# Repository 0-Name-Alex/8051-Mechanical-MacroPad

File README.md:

# ⌨️ 8051 Mechanical Macro Pad

<div align="center">

**A custom mechanical macro keypad engineered around the classic 8051 microcontroller architecture.**  
Designed in KiCad EDA — featuring mechanical switch matrix, diode isolation, and programmable macro functionality.

[-orange)](#)

</div>

---

## 🎯 Project Overview

This project is a dedicated **hardware macro pad** powered by an 8051 microcontroller. Designed for productivity, gaming macros, and shortcut triggering, it provides tactile mechanical switch input with hardware-level debouncing and matrix scanning.

### ✨ Hardware Highlights

- 🔘 **Mechanical Switches**: Footprints compatible with standard Cherry MX / Kailh / Gateron style switches.
- ⚡ **Anti-Ghosting Matrix**: Individual diode isolation for each switch, supporting N-key rollover across macro triggers.
- 🧠 **8051 Core**: Demonstrates hardware implementation and register-level firmware scanning on the classic embedded 8051 architecture.
- 📐 **Compact Form Factor**: Designed for minimal desktop footprint alongside a primary keyboard.

---

## 📊 Development Status

```
[████████████████████] 100%  Schematic Design & Netlist (Done)
[██████████████░░░░░░]  70%  PCB Layout & Trace Routing (In Progress 🔄)
[░░░░░░░░░░░░░░░░░░░░]   0%  Final Fabrication Gerbers & BOM (Upcoming)
[░░░░░░░░░░░░░░░░░░░░]   0%  Firmware Implementation & Keymapping (Upcoming)
```

> ⚠️ **Note:** This project is actively being routed and finalized in KiCad. Final revision Gerbers and assembly photos will be added upon manufacturing!

---

## 📁 Repository Files

| File | Description |
|---|---|
| `MEchanical Macro pad.kicad_pro` | Master KiCad project file |
| `MEchanical Macro pad.kicad_sch` | Full electrical schematic diagram & switch matrix netlist |
| `MEchanical Macro pad.kicad_pcb` | Board layout, copper traces, footprints, and silk screen |

---

## 🛠️ Opening the Project

1. Install [**KiCad EDA**](https://www.kicad.org/) (version 7.0 or later recommended).
2. Clone this repository:
   ```bash
   git clone https://github.com/0-Name-Alex/8051-Mechanical-MacroPad.git
   ```
3. Open `MEchanical Macro pad.kicad_pro` in KiCad to view both the schematic and PCB layout editor.

---

## 📄 License

Open-source hardware project licensed under the MIT License.

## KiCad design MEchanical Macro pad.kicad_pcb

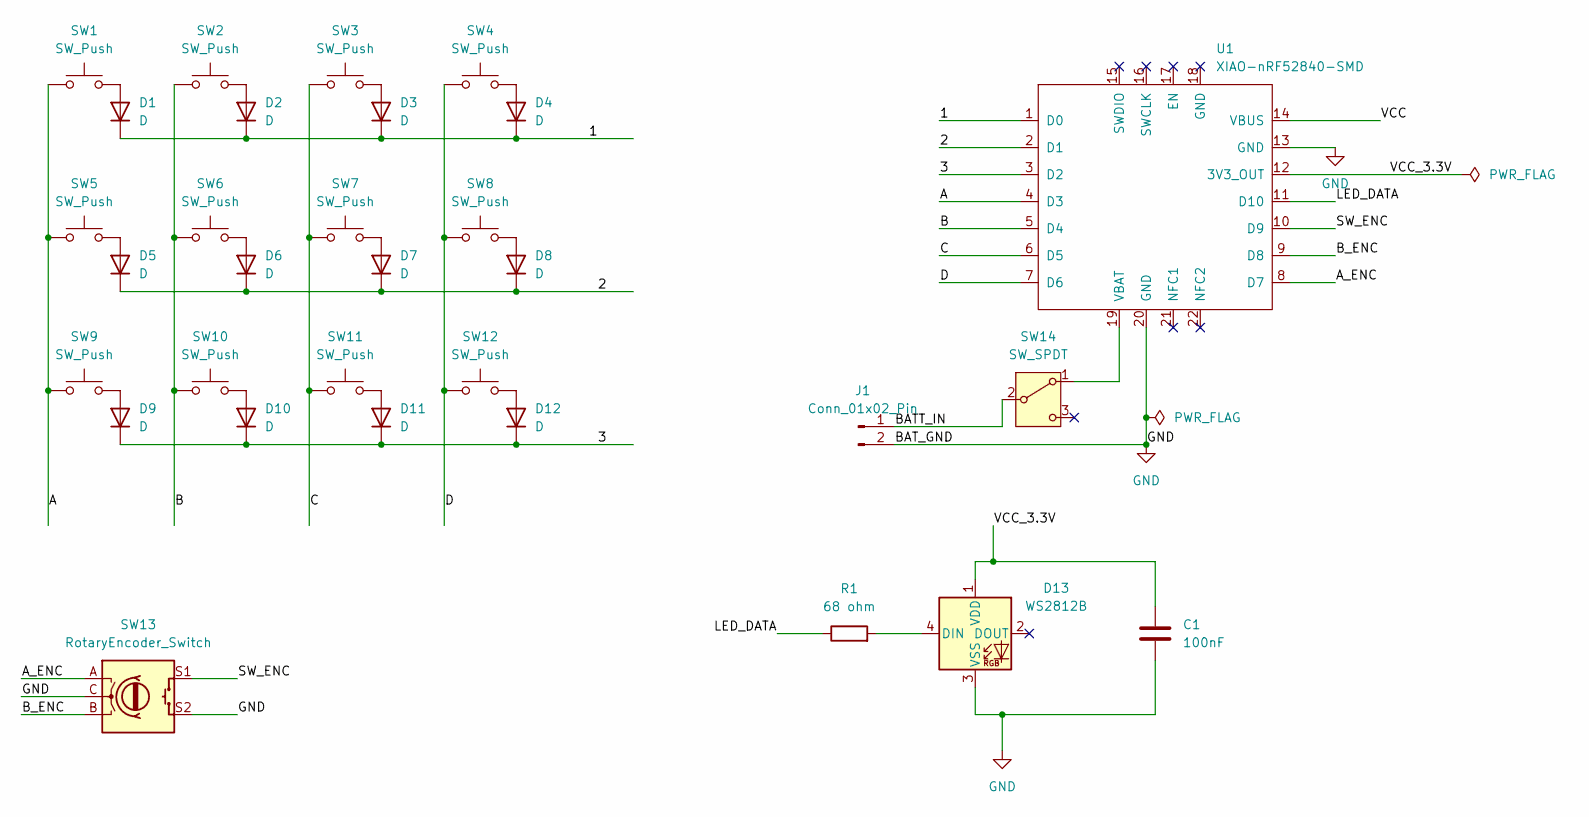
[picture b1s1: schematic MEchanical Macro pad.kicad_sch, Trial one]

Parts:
C1: 100nF; C_0805_2012Metric
D1, D2, D3, D4, D5, D6, D7, D8, D9, D10, D11, D12: D; D_DO-35_SOD27_P7.62mm_Horizontal
D13: WS2812B; LED_WS2812B_PLCC4_5.0x5.0mm_P3.2mm
J1: Conn_01x02_Pin; JST_PH_S2B-PH-K_1x02_P2.00mm_Horizontal
R1: 68 ohm; R_0805_2012Metric
SW1, SW2, SW3, SW4, SW5, SW6, SW7, SW8, SW9, SW10, SW11, SW12: SW_Push; SW_Cherry_MX_1.00u_PCB
SW13: RotaryEncoder_Switch; RotaryEncoder_Alps_EC11E-Switch_Vertical_H20mm_MountingHoles
SW14: SW_SPDT; SW_DIP_SPSTx01_Piano_10.8x4.1mm_W7.62mm_P2.54mm
U1: XIAO-nRF52840-SMD

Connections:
/1: D1.1 (K), D2.1 (K), D3.1 (K), D4.1 (K), U1.1 (D0)
/2: D5.1 (K), D6.1 (K), D7.1 (K), D8.1 (K), U1.2 (D1)
/3: D9.1 (K), D10.1 (K), D11.1 (K), D12.1 (K), U1.3 (D2)
/A: SW1.1, SW5.1, SW9.1, U1.4 (D3)
/A_ENC: SW13.A, U1.8 (D7)
/B: SW2.1, SW6.1, SW10.1, U1.5 (D4)
/BATT_IN: J1.1, SW14.2 (B)
/B_ENC: SW13.B, U1.9 (D8)
/C: SW3.1, SW7.1, SW11.1, U1.6 (D5)
/D: SW4.1, SW8.1, SW12.1, U1.7 (D6)
/LED_DATA: R1.1, U1.11 (D10)
/SW_ENC: SW13.S1, U1.10 (D9)
/VCC: U1.14 (VBUS)
/VCC_3.3V: C1.1, D13.1 (VDD), U1.12 (3V3_OUT)
GND: C1.2, D13.3 (VSS), J1.2, SW13.C, SW13.S2, U1.13 (GND), U1.20 (GND)
unnamed: D1.2 (A), SW1.2
unnamed: D2.2 (A), SW2.2
unnamed: D3.2 (A), SW3.2
unnamed: D4.2 (A), SW4.2
unnamed: D5.2 (A), SW5.2
unnamed: D6.2 (A), SW6.2
unnamed: D7.2 (A), SW7.2
unnamed: D8.2 (A), SW8.2
unnamed: D9.2 (A), SW9.2
unnamed: D10.2 (A), SW10.2
unnamed: D11.2 (A), SW11.2
unnamed: D12.2 (A), SW12.2
unnamed: D13.4 (DIN), R1.2
unnamed: SW14.1 (A), U1.19 (VBAT)

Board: 2 copper layers, 31 parts (0 on the bottom side), 28 nets, no tracks yet.

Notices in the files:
README.md:
License: MIT
